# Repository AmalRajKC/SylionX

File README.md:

# SylionX — CANFD2USB

An open source USB to CAN FD adapter for real-time CAN bus monitoring, 
diagnostics, and frame injection.

## Repository Structure

| Folder | Contents | License |
|--------|----------|---------|
| `CANFD2USB_Hardware` | KiCad schematics, PCB layout, BOM, gerbers | CERN OHL-S v2 |
| `CANFD2USB_Firmware` | TI MSPM0G3507 C firmware | MIT |
| `CANtrace` | CANtrace Qt6/C++ desktop app | MIT |

## Hardware — CANFD2USB
- Microcontroller: TI MSPM0G3507
- CAN Protocol: Classic CAN + CAN FD (ISO 11898-1)
- Data Rate: Up to 5 Mbps (CAN FD)
- Interface: USB-C (USB 2.0)
- Power: USB powered (5V)
- OS: Windows (Linux planned)

## Getting Started
See [docs/quickstart.md](docs/quickstart.md) for build and setup instructions.

## License
- **Software & Firmware** — [MIT License](LICENSE-MIT.txt)
- **Hardware** — [CERN Open Hardware Licence v2 - Strongly Reciprocal](LICENSE-CERN-OHL-S-v2.txt)

## Issues & Feedback
Found a bug or have a feature request? 
[Open an issue](https://github.com/AmalRajKC/SylionX/issues) — all feedback is welcome.

> **Note:** This repository does not accept pull requests at this time.
> The codebase is open source for transparency and learning — feel free to fork
> and build your own version.

⚠️ Windows SmartScreen may show a warning on first run.
Click "More info" → "Run anyway" to proceed.
This is expected for new unsigned software.
Source code is fully open — you can build from source if preferred.

---
© 2026 SylionX / Amal Raj KC

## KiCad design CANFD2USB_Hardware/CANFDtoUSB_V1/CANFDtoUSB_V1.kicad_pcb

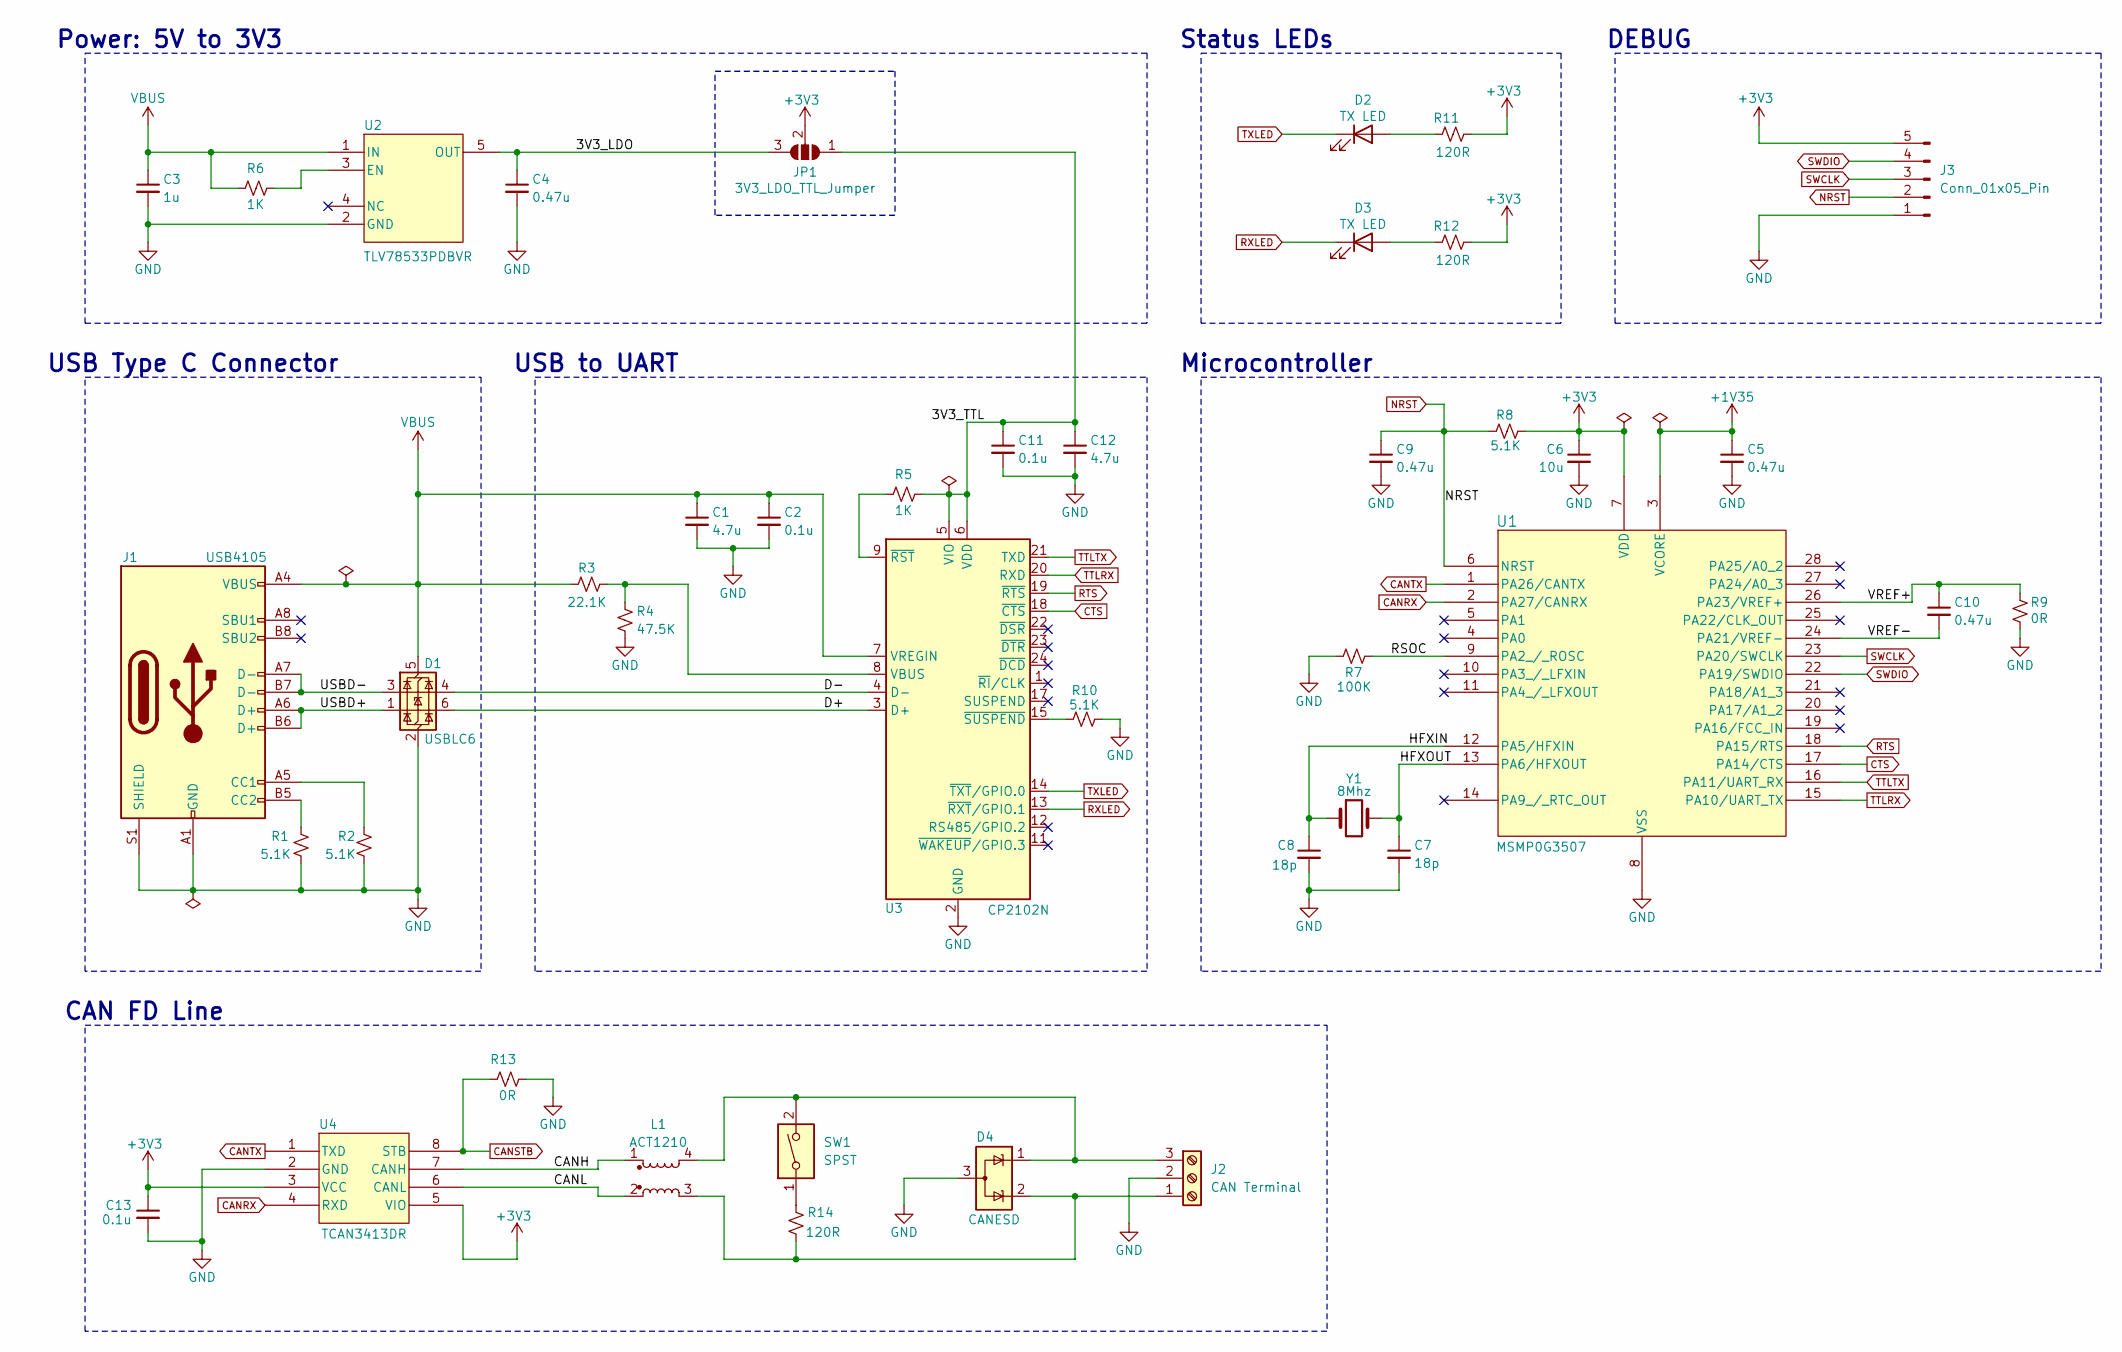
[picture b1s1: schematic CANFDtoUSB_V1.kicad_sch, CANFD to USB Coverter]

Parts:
C1, C12: 4.7u; C_0805_2012Metric_Pad1.18x1.45mm_HandSolder; Part Number GRM21BR71C475KE51K
C2, C11, C13: 0.1u; C_0603_1608Metric_Pad1.08x0.95mm_HandSolder; Part Number CC0603KPX7R7BB104
C3: 1u; C_0805_2012Metric_Pad1.18x1.45mm_HandSolder; Part Number CL21B105KOFNNNF
C4, C5, C9, C10: 0.47u; C_0603_1608Metric_Pad1.08x0.95mm_HandSolder; Part Number CL10B474KO8NNNC
C6: 10u; C_0805_2012Metric_Pad1.18x1.45mm_HandSolder; Part Number CL21A106KOQNNNF
C7, C8: 18p; C_0603_1608Metric_Pad1.08x0.95mm_HandSolder; Part Number CC0603GRNPO9BN180
D1: USBLC6; SOT-23-6; Part Number USBLC6-2P6
D2, D3: TX LED; LED_0603_1608Metric_Pad1.05x0.95mm_HandSolder; Part Number 19-217/BHC-ZL1M2RY/6T
D4: CANESD; SOT-323_SC-70; Part Number SP0502BAHTG
J1: USB4105; USB_C_Receptacle_GCT_USB4105-xx-A_16P_TopMnt_Horizontal; Part Number USB4105-GF-A-120
J2: CAN Terminal; TerminalBlock_Phoenix_PT-1,5-3-3.5-H_1x03_P3.50mm_Horizontal; Part Number YO0301500000G
J3: Conn_01x05_Pin; PinHeader_1x05_P2.54mm_Vertical
JP1: 3V3_LDO_TTL_Jumper; SolderJumper-3_P1.3mm_Open_RoundedPad1.0x1.5mm_NumberLabels
L1: ACT1210; ACT1210D-101-2P-TL00; Part Number ACT1210D-101-2P-TL00
R1, R2, R8, R10: 5.1K; R_0603_1608Metric_Pad0.98x0.95mm_HandSolder; Part Number RC0603FR-135K1L
R3: 22.1K; R_0603_1608Metric_Pad0.98x0.95mm_HandSolder; Part Number RC0603FR-0722K1L
R4: 47.5K; R_0603_1608Metric_Pad0.98x0.95mm_HandSolder; Part Number RC0603FR-0747K5L
R5, R6: 1K; R_0603_1608Metric_Pad0.98x0.95mm_HandSolder; Part Number RC0603FR-0722K1L
R7: 100K; R_0603_1608Metric_Pad0.98x0.95mm_HandSolder; Part Number ERA3AEB104V
R9, R13: 0R; R_0603_1608Metric_Pad0.98x0.95mm_HandSolder; Part Number AC0603JR-130RL
R11, R12, R14: 120R; R_0603_1608Metric_Pad0.98x0.95mm_HandSolder; Part Number RC0603FR-13120RL
SW1: SPST; SW_DIP_SPSTx01_Slide_Copal_CHS-01A_W5.08mm_P1.27mm_JPin; Part Number CHS-01A
U1: MSMP0G3507; VSSOP28_DGS_TEX; Part Number MSPM0G3507SDGS28R
U2: TLV78533PDBVR; SOT-23-5_HandSoldering; Part Number TLV78533PDBVR
U3: CP2102N; QFN-24-1EP_4x4mm_P0.5mm_EP2.6x2.6mm_ThermalVias; Part Number CP2102N-A02-GQFN24R
U4: TCAN3413DR; SOIC8_D_TEX; Part Number TCAN3413DR
Y1: 8Mhz; Crystal_SMD_Abracon_ABM3-2Pin_5.0x3.2mm; Part Number ABM3-8.000MHZ-D2Y-T

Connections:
+1V35: C5.1, U1.3 (VCORE)
+3V3: C6.1, C13.1, J3.5, JP1.2 (C), R8.2, R11.2, R12.2, U1.7 (VDD), U4.3 (VCC), U4.5 (VIO)
/3V3_LDO: C4.1, JP1.3 (B), U2.5 (OUT)
/3V3_TTL: C11.1, C12.1, JP1.1 (A), R5.2, U3.5 (VIO), U3.6 (VDD)
/CANH: L1.1, U4.7 (CANH)
/CANL: L1.2, U4.6 (CANL)
/D+: D1.6 (I/O1), U3.3 (D+)
/D-: D1.4 (I/O2), U3.4 (D-)
/HFXIN: C8.1, U1.12 (PA5/HFXIN), Y1.1
/HFXOUT: C7.1, U1.13 (PA6/HFXOUT), Y1.2
/RSOC: R7.2, U1.9 (PA2_/_ROSC)
/USBD+: D1.1 (I/O1), J1.A6 (D+), J1.B6 (D+)
/USBD-: D1.3 (I/O2), J1.A7 (D-), J1.B7 (D-)
/VREF+: C10.1, R9.2, U1.26 (PA23/VREF+)
/VREF-: C10.2, U1.24 (PA21/VREF-)
CANRX: U1.2 (PA27/CANRX), U4.4 (RXD)
CANSTB: R13.1, U4.8 (STB)
CANTX: U1.1 (PA26/CANTX), U4.1 (TXD)
CTS: U1.17 (PA14/CTS), U3.18 (~CTS)
GND: C1.2, C2.2, C3.2, C4.2, C5.2, C6.2, C7.2, C8.2, C9.2, C11.2, C12.2, C13.2, D1.2 (GND), D4.3 (A), J1.A1 (GND), J1.A12 (GND), J1.B1 (GND), J1.B12 (GND), J1.S1 (SHIELD), J2.2, J3.1, R1.2, R2.2, R4.2, R7.1, R9.1, R10.2, R13.2, U1.8 (VSS), U2.2 (GND), U3.2 (GND), U3.25 (GND), U4.2 (GND)
NRST: C9.1, J3.2, R8.1, U1.6 (NRST)
unnamed: D2.2 (A), R11.1
unnamed: D3.2 (A), R12.1
unnamed: J1.A5 (CC1), R2.1
unnamed: J1.B5 (CC2), R1.1
unnamed: D4.2 (K), J2.1, L1.3, R14.2
unnamed: D4.1 (K), J2.3, L1.4, SW1.2
unnamed: R14.1, SW1.1
unnamed: R6.2, U2.3 (EN)
unnamed: R3.2, R4.1, U3.8 (VBUS)
unnamed: R5.1, U3.9 (~RST)
unnamed: R10.1, U3.15 (~SUSPEND)
RTS: U1.18 (PA15/RTS), U3.19 (~RTS)
RXLED: D3.1 (K), U3.13 (~RXT/GPIO.1)
SWCLK: J3.3, U1.23 (PA20/SWCLK)
SWDIO: J3.4, U1.22 (PA19/SWDIO)
TTLRX: U1.15 (PA10/UART_TX), U3.20 (RXD)
TTLTX: U1.16 (PA11/UART_RX), U3.21 (TXD)
TXLED: D2.1 (K), U3.14 (~TXT/GPIO.0)
VBUS: C1.1, C2.1, C3.1, D1.5 (VBUS), J1.A4 (VBUS), J1.A9 (VBUS), J1.B4 (VBUS), J1.B9 (VBUS), R3.1, R6.1, U2.1 (IN), U3.7 (VREGIN)

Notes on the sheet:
Microcontroller
USB to UART
DEBUG
Power: 5V to 3V3
Status LEDs
CAN FD Line
USB Type C Connector

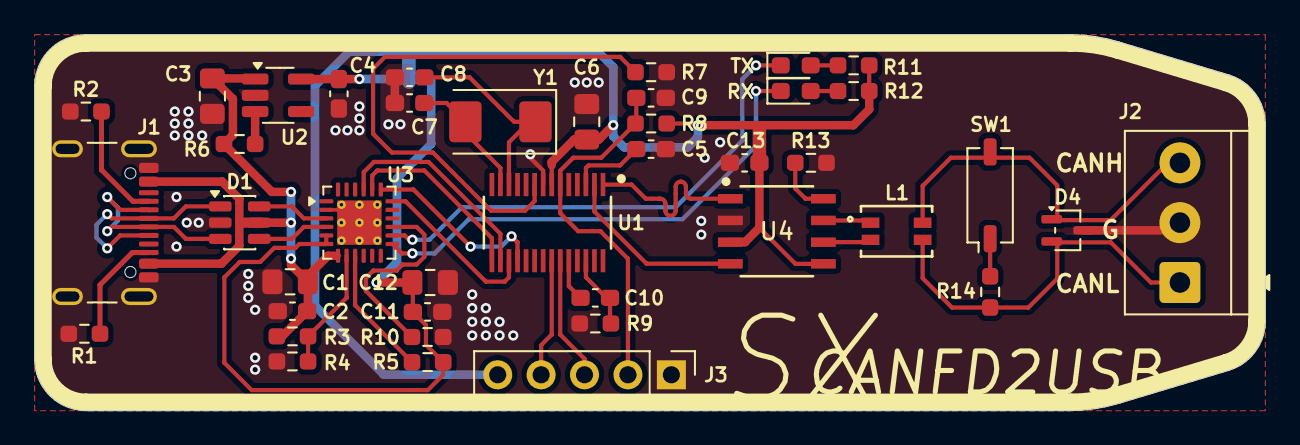
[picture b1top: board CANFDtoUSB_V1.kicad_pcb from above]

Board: 2 copper layers, 72.0 x 22.0 mm, 42 parts (1 on the bottom side), 40 nets.

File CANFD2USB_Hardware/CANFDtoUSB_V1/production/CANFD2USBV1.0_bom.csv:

Designator,Footprint,Quantity,Value,LCSC Part #
"C1, C12",0805,2,4.7u,
"C10, C4, C5, C9",0603,4,0.47u,
"C11, C13, C2",0603,3,0.1u,
C3,0805,1,1u,
C6,0805,1,10u,
"C7, C8",0603,2,27p,
D1,SOT-23-6,1,USBLC6-2SC6,
"D2, D3",0603,2,TX LED,
D4,SOT-323_SC-70,1,CANESD,
J1,USB4105,1,USB4105,
J2,DNP,1,DNP,
J3,DNP,1,DNP,
L1,ACT1210D-101-2P-TL00,1,ACT1210,
"R1, R10, R2, R8",0603,4,5.1K,
"R11, R12, R14",0603,3,120R,
"R13, R9",0603,2,0R,
R3,0603,1,22.1K,
R4,0603,1,47.5K,
"R5, R6",0603,2,1K,
R7,0603,1,100K,
SW1,CHS-01A,1,SPST,
U1,VSSOP28_DGS_TEX,1,MSMP0G3507,
U2,SOT-23-5_HandSoldering,1,TLV78533PDBVR,
U3,QFN-24-1EP,1,CP2102N,
U4,SOIC8_D_TEX,1,TCAN3413DR,
Y1,2Pin_5.0x3.2mm,1,ABM3,

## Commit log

2026-05-31 Initial commit — README, licenses, folder structure
2026-05-31 Add hardware, firmware, and software source files
